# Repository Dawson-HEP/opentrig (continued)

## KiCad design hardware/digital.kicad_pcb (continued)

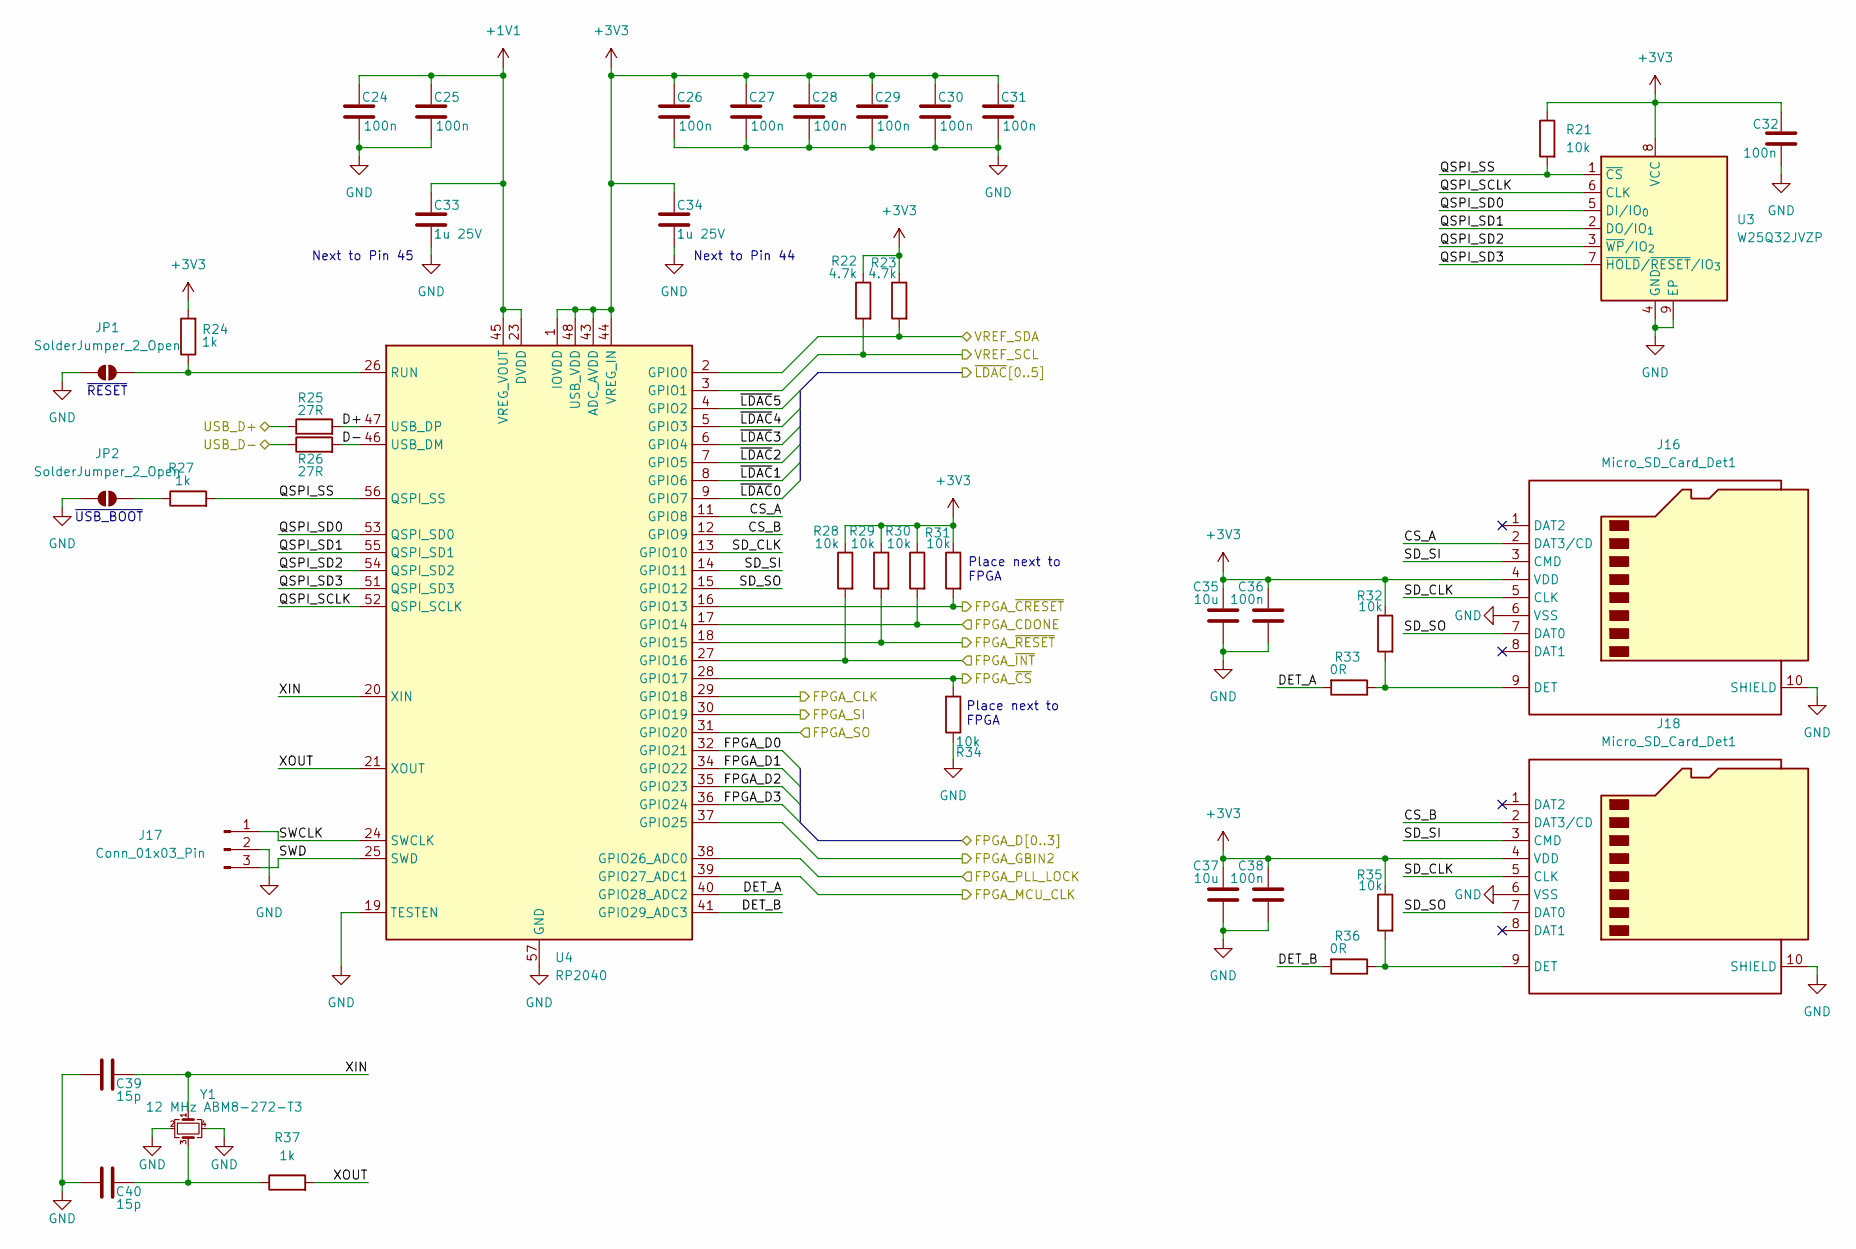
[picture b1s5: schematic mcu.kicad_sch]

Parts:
C24, C25, C26, C27, C28, C29, C30, C31, C32, C36, C38: 100n; C_0402_1005Metric; LCSC C307331
C33, C34: 1u 25V; C_0402_1005Metric; LCSC C52923
C35, C37: 10u; C_1206_3216Metric; LCSC C13585
C39, C40: 15p; C_0402_1005Metric; LCSC C1548
J16, J18: Micro_SD_Card_Det1; microSD_HC_MSD-4-A; LCSC C91145
J17: Conn_01x03_Pin; PinHeader_1x03_P2.54mm_Vertical
JP1, JP2: SolderJumper_2_Open; SolderJumper-2_P1.3mm_Open_RoundedPad1.0x1.5mm
R21, R28, R29, R30, R31, R32, R34, R35: 10k; R_0402_1005Metric; LCSC C25744
R22, R23: 4.7k; R_0402_1005Metric; LCSC C25900
R24, R27, R37: 1k; R_0402_1005Metric; LCSC C11702
R25, R26: 27R; R_0402_1005Metric; LCSC C138021
R33, R36: 0R; R_0402_1005Metric; LCSC C17168
U3: W25Q32JVZP; WSON-8-1EP_6x5mm_P1.27mm_EP3.4x4.3mm; LCSC C571260
U4: RP2040; QFN-56-1EP_7x7mm_P0.4mm_EP3.2x3.2mm; LCSC C2040
Y1: 12 MHz ABM8-272-T3; Crystal_SMD_Abracon_ABM8AIG-4Pin_3.2x2.5mm; LCSC C20625731

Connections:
+1V1: C24.1, C25.1, C33.1, U4.23 (DVDD), U4.45 (VREG_VOUT), U4.50 (DVDD)
+3V3: C26.1, C27.1, C28.1, C29.1, C30.1, C31.1, C32.1, C34.1, C35.1, C36.1, C37.1, C38.1, J16.4 (VDD), J18.4 (VDD), R21.1, R22.1, R23.1, R24.2, R28.1, R29.1, R30.1, R31.1, R32.1, R35.1, U3.8 (VCC), U4.1 (IOVDD), U4.10 (IOVDD), U4.22 (IOVDD), U4.33 (IOVDD), U4.42 (IOVDD), U4.43 (ADC_AVDD), U4.44 (VREG_IN), U4.48 (USB_VDD), U4.49 (IOVDD); also elsewhere on the board
/FPGA/CDONE: R30.2, U4.17 (GPIO14); also elsewhere on the board
/FPGA/CS: R34.2, U4.28 (GPIO17); also elsewhere on the board
/FPGA/D0: U4.32 (GPIO21); also elsewhere on the board
/FPGA/D1: U4.34 (GPIO22); also elsewhere on the board
/FPGA/D2: U4.35 (GPIO23); also elsewhere on the board
/FPGA/D3: U4.36 (GPIO24); also elsewhere on the board
/FPGA/GBIN2: U4.37 (GPIO25); also elsewhere on the board
/FPGA/MCU_CLK: U4.39 (GPIO27_ADC1); also elsewhere on the board
/FPGA/PLL_LOCK: U4.38 (GPIO26_ADC0); also elsewhere on the board
/FPGA/SCK: U4.29 (GPIO18); also elsewhere on the board
/FPGA/SI: U4.30 (GPIO19); also elsewhere on the board
/FPGA/SO: U4.31 (GPIO20); also elsewhere on the board
/FPGA/~CRESET: R31.2, U4.16 (GPIO13); also elsewhere on the board
/FPGA/~INT: R28.2, U4.27 (GPIO16); also elsewhere on the board
/FPGA/~RESET: R29.2, U4.18 (GPIO15); also elsewhere on the board
/MCU/CS_A: J16.2 (DAT3/CD), U4.11 (GPIO8)
/MCU/CS_B: J18.2 (DAT3/CD), U4.12 (GPIO9)
/MCU/D+: R25.2, U4.47 (USB_DP)
/MCU/D-: R26.2, U4.46 (USB_DM)
/MCU/DET_A: R33.2, U4.40 (GPIO28_ADC2)
/MCU/DET_B: R36.2, U4.41 (GPIO29_ADC3)
/MCU/QSPI_SCLK: U3.6 (CLK), U4.52 (QSPI_SCLK)
/MCU/QSPI_SD0: U3.5 (DI/IO_{0}), U4.53 (QSPI_SD0)
/MCU/QSPI_SD1: U3.2 (DO/IO_{1}), U4.55 (QSPI_SD1)
/MCU/QSPI_SD2: U3.3 (~WP/IO_{2}), U4.54 (QSPI_SD2)
/MCU/QSPI_SD3: U3.7 (~HOLD/~RESET/IO_{3}), U4.51 (QSPI_SD3)
/MCU/QSPI_SS: R21.2, R27.2, U3.1 (~CS), U4.56 (QSPI_SS)
/MCU/SD_CLK: J16.5 (CLK), J18.5 (CLK), U4.13 (GPIO10)
/MCU/SD_SI: J16.3 (CMD), J18.3 (CMD), U4.14 (GPIO11)
/MCU/SD_SO: J16.7 (DAT0), J18.7 (DAT0), U4.15 (GPIO12)
/MCU/SWCLK: J17.1, U4.24 (SWCLK)
/MCU/SWD: J17.3, U4.25 (SWD)
/MCU/USB_D+: R25.1; also elsewhere on the board
/MCU/USB_D-: R26.1; also elsewhere on the board
/MCU/VREF_SCL: R22.2, U4.3 (GPIO1); also elsewhere on the board
/MCU/VREF_SDA: R23.2, U4.2 (GPIO0); also elsewhere on the board
/MCU/XIN: C39.2, U4.20 (XIN), Y1.1
/MCU/XOUT: R37.2, U4.21 (XOUT)
/MCU/~LDAC0: U4.9 (GPIO7); also elsewhere on the board
/MCU/~LDAC1: U4.8 (GPIO6); also elsewhere on the board
/MCU/~LDAC2: U4.7 (GPIO5); also elsewhere on the board
/MCU/~LDAC3: U4.6 (GPIO4); also elsewhere on the board
/MCU/~LDAC4: U4.5 (GPIO3); also elsewhere on the board
/MCU/~LDAC5: U4.4 (GPIO2); also elsewhere on the board
GND: C24.2, C25.2, C26.2, C27.2, C28.2, C29.2, C30.2, C31.2, C32.2, C33.2, C34.2, C35.2, C36.2, C37.2, C38.2, C39.1, C40.1, J16.6 (VSS), J16.10 (SHIELD), J17.2, J18.6 (VSS), J18.10 (SHIELD), JP1.1 (A), JP2.1 (A), R34.1, U3.4 (GND), U3.9 (EP), U4.19 (TESTEN), U4.57 (GND), Y1.2, Y1.4; also elsewhere on the board
unnamed: C40.2, R37.1, Y1.3
unnamed: J16.9 (DET), R32.2, R33.1
unnamed: J18.9 (DET), R35.2, R36.1
unnamed: JP1.2 (B), R24.1, U4.26 (RUN)
unnamed: JP2.2 (B), R27.1

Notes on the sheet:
Place next to FPGA
Next to Pin 44
Next to Pin 45
~{USB_BOOT}
~{RESET}

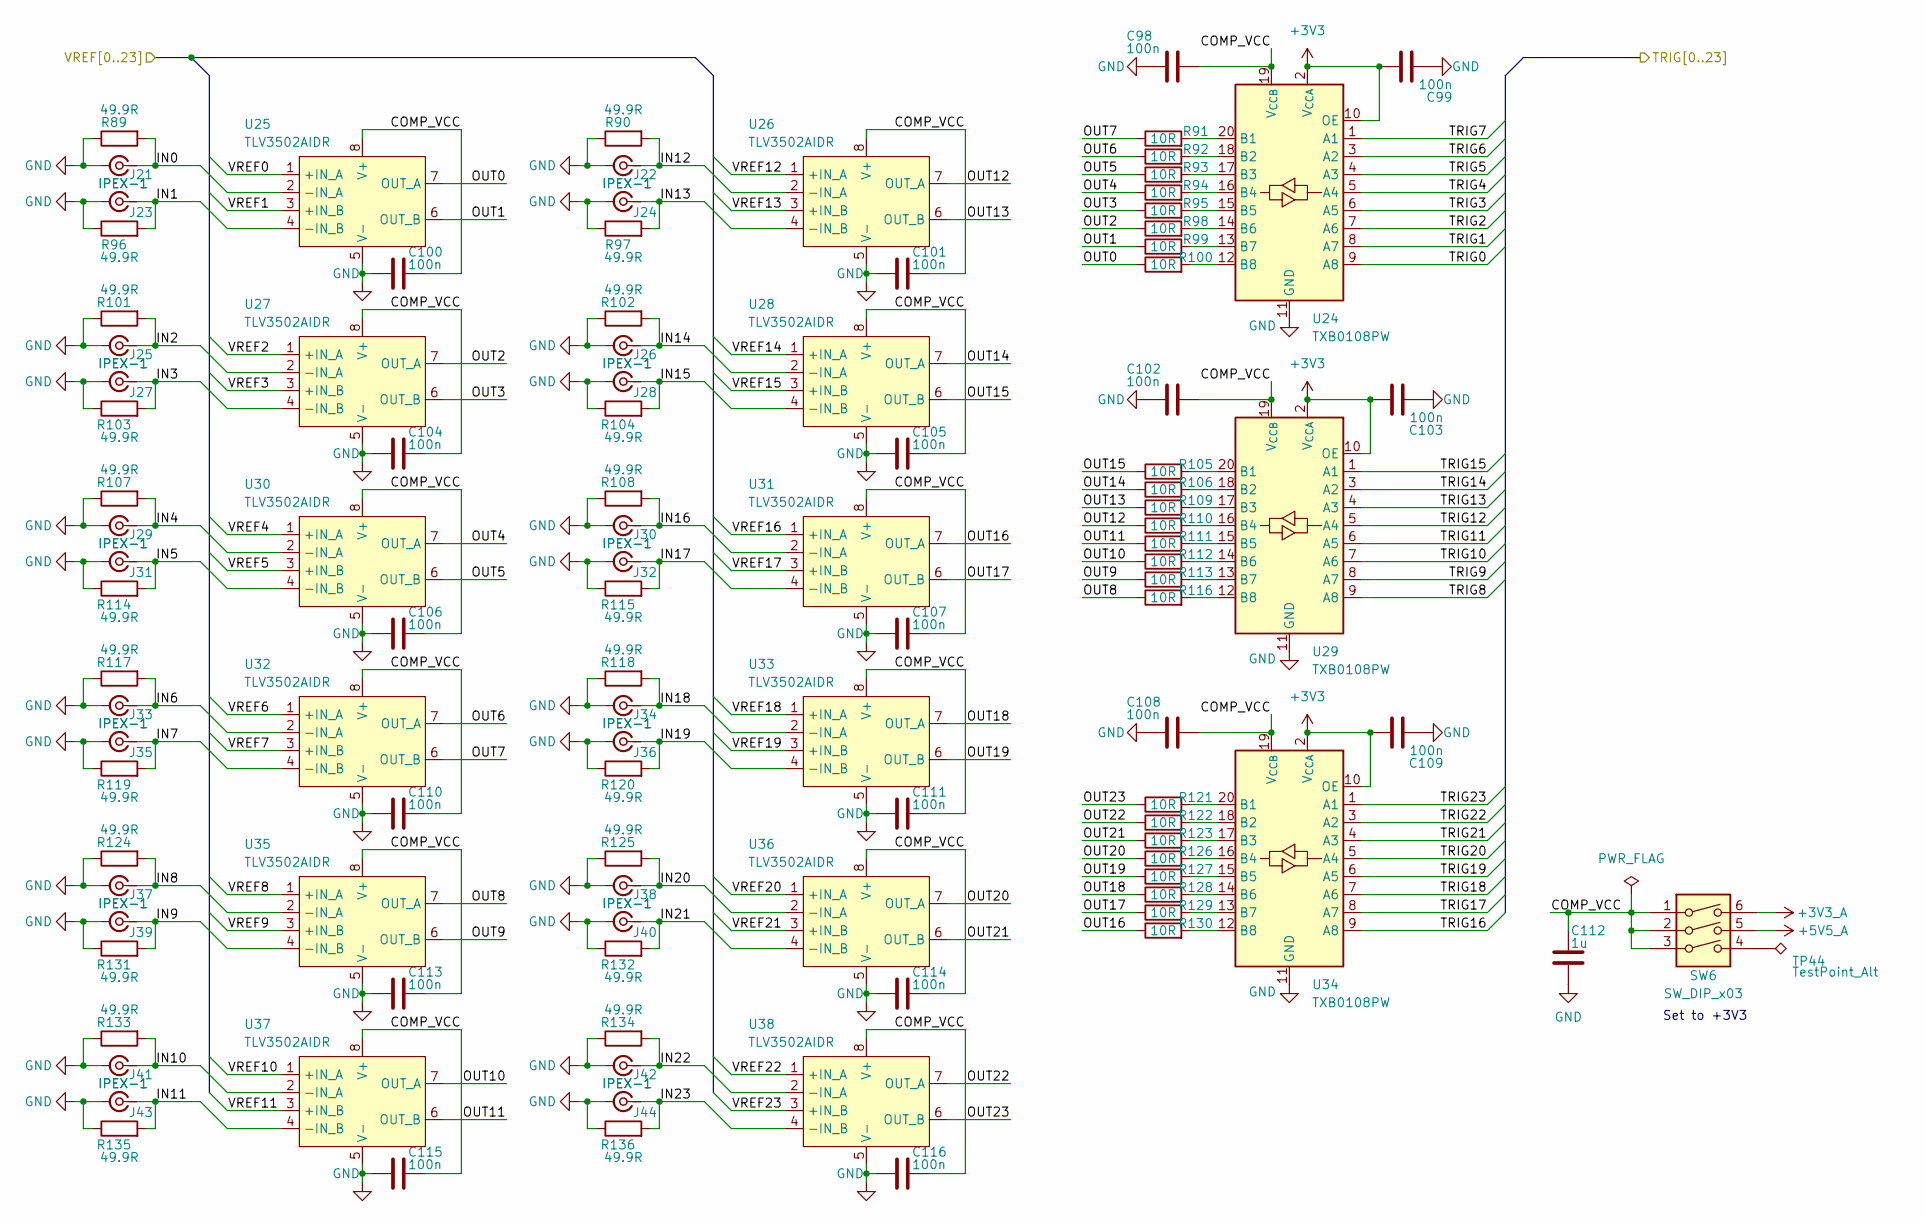
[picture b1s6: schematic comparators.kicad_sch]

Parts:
C98, C99, C100, C101, C102, C103, C104, C105, C106, C107, C108, C109, C110, C111, C113, C114, C115, C116: 100n; C_0402_1005Metric; LCSC C307331
C112: 1u; C_0805_2012Metric; LCSC C28323
J21, J22, J23, J24, J25, J26, J27, J28, J29, J30, J31, J32, J33, J34, J35, J36, J37, J38, J39, J40, J41, J42, J43, J44: IPEX-1; BWIPX-1-001E; LCSC C496552
R89, R90, R96, R97, R101, R102, R103, R104, R107, R108, R114, R115, R117, R118, R119, R120, R124, R125, R131, R132, R133, R134, R135, R136: 49.9R; R_0603_1608Metric; LCSC C23185
R91, R92, R93, R94, R95, R98, R99, R100, R105, R106, R109, R110, R111, R112, R113, R116, R121, R122, R123, R126, R127, R128, R129, R130: 10R; R_0402_1005Metric; LCSC C25077
SW6: SW_DIP_x03; SW_DIP_SPSTx03_Slide_6.7x9.18mm_W8.61mm_P2.54mm_LowProfile; LCSC C129079
TP44: TestPoint_Alt; TestPoint_Keystone_5015_Micro_Mini; LCSC C159868
U24, U29, U34: TXB0108PW; TSSOP-20_4.4x6.5mm_P0.65mm; LCSC C53406
U25, U26, U27, U28, U30, U31, U32, U33, U35, U36, U37, U38: TLV3502AIDR; SOIC-8_3.9x4.9mm_P1.27mm

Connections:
+3V3: C99.1, C103.1, C109.1, U24.2 (V_{CCA}), U24.10 (OE), U29.2 (V_{CCA}), U29.10 (OE), U34.2 (V_{CCA}), U34.10 (OE); also elsewhere on the board
+3V3_A: SW6.6; also elsewhere on the board
+5V5_A: SW6.5; also elsewhere on the board
/FPGA/TRIG_IN_0: U24.9 (A8); also elsewhere on the board
/FPGA/TRIG_IN_1: U24.8 (A7); also elsewhere on the board
/FPGA/TRIG_IN_2: U24.7 (A6); also elsewhere on the board
/FPGA/TRIG_IN_3: U24.6 (A5); also elsewhere on the board
/FPGA/TRIG_IN_4: U24.5 (A4); also elsewhere on the board
/FPGA/TRIG_IN_5: U24.4 (A3); also elsewhere on the board
/FPGA/TRIG_IN_6: U24.3 (A2); also elsewhere on the board
/FPGA/TRIG_IN_7: U24.1 (A1); also elsewhere on the board
/FPGA/TRIG_IN_8: U29.9 (A8); also elsewhere on the board
/FPGA/TRIG_IN_9: U29.8 (A7); also elsewhere on the board
/FPGA/TRIG_IN_10: U29.7 (A6); also elsewhere on the board
/FPGA/TRIG_IN_11: U29.6 (A5); also elsewhere on the board
/FPGA/TRIG_IN_12: U29.5 (A4); also elsewhere on the board
/FPGA/TRIG_IN_13: U29.4 (A3); also elsewhere on the board
/FPGA/TRIG_IN_14: U29.3 (A2); also elsewhere on the board
/FPGA/TRIG_IN_15: U29.1 (A1); also elsewhere on the board
/FPGA/TRIG_IN_16: U34.9 (A8); also elsewhere on the board
/FPGA/TRIG_IN_17: U34.8 (A7); also elsewhere on the board
/FPGA/TRIG_IN_18: U34.7 (A6); also elsewhere on the board
/FPGA/TRIG_IN_19: U34.6 (A5); also elsewhere on the board
/FPGA/TRIG_IN_20: U34.5 (A4); also elsewhere on the board
/FPGA/TRIG_IN_21: U34.4 (A3); also elsewhere on the board
/FPGA/TRIG_IN_22: U34.3 (A2); also elsewhere on the board
/FPGA/TRIG_IN_23: U34.1 (A1); also elsewhere on the board
/comparators/COMP_VCC: C98.1, C100.2, C101.2, C102.1, C104.2, C105.2, C106.2, C107.2, C108.1, C110.2, C111.2, C112.1, C113.2, C114.2, C115.2, C116.2, SW6.1, SW6.2, SW6.3, U24.19 (V_{CCB}), U25.8 (V+), U26.8 (V+), U27.8 (V+), U28.8 (V+), U29.19 (V_{CCB}), U30.8 (V+), U31.8 (V+), U32.8 (V+), U33.8 (V+), U34.19 (V_{CCB}), U35.8 (V+), U36.8 (V+), U37.8 (V+), U38.8 (V+)
/comparators/IN0: J21.1 (In), R89.2, U25.2 (-IN_A)
/comparators/IN1: J23.1 (In), R96.2, U25.4 (-IN_B)
/comparators/IN2: J25.1 (In), R101.2, U27.2 (-IN_A)
/comparators/IN3: J27.1 (In), R103.2, U27.4 (-IN_B)
/comparators/IN4: J29.1 (In), R107.2, U30.2 (-IN_A)
/comparators/IN5: J31.1 (In), R114.2, U30.4 (-IN_B)
/comparators/IN6: J33.1 (In), R117.2, U32.2 (-IN_A)
/comparators/IN7: J35.1 (In), R119.2, U32.4 (-IN_B)
/comparators/IN8: J37.1 (In), R124.2, U35.2 (-IN_A)
/comparators/IN9: J39.1 (In), R131.2, U35.4 (-IN_B)
/comparators/IN10: J41.1 (In), R133.2, U37.2 (-IN_A)
/comparators/IN11: J43.1 (In), R135.2, U37.4 (-IN_B)
/comparators/IN12: J22.1 (In), R90.2, U26.2 (-IN_A)
/comparators/IN13: J24.1 (In), R97.2, U26.4 (-IN_B)
/comparators/IN14: J26.1 (In), R102.2, U28.2 (-IN_A)
/comparators/IN15: J28.1 (In), R104.2, U28.4 (-IN_B)
/comparators/IN16: J30.1 (In), R108.2, U31.2 (-IN_A)
/comparators/IN17: J32.1 (In), R115.2, U31.4 (-IN_B)
/comparators/IN18: J34.1 (In), R118.2, U33.2 (-IN_A)
/comparators/IN19: J36.1 (In), R120.2, U33.4 (-IN_B)
/comparators/IN20: J38.1 (In), R125.2, U36.2 (-IN_A)
/comparators/IN21: J40.1 (In), R132.2, U36.4 (-IN_B)
/comparators/IN22: J42.1 (In), R134.2, U38.2 (-IN_A)
/comparators/IN23: J44.1 (In), R136.2, U38.4 (-IN_B)
/comparators/OUT0: R100.1, U25.7 (OUT_A)
/comparators/OUT1: R99.1, U25.6 (OUT_B)
/comparators/OUT2: R98.1, U27.7 (OUT_A)
/comparators/OUT3: R95.1, U27.6 (OUT_B)
/comparators/OUT4: R94.1, U30.7 (OUT_A)
/comparators/OUT5: R93.1, U30.6 (OUT_B)
/comparators/OUT6: R92.1, U32.7 (OUT_A)
/comparators/OUT7: R91.1, U32.6 (OUT_B)
/comparators/OUT8: R116.1, U35.7 (OUT_A)
/comparators/OUT9: R113.1, U35.6 (OUT_B)
/comparators/OUT10: R112.1, U37.7 (OUT_A)
/comparators/OUT11: R111.1, U37.6 (OUT_B)
/comparators/OUT12: R110.1, U26.7 (OUT_A)
/comparators/OUT13: R109.1, U26.6 (OUT_B)
/comparators/OUT14: R106.1, U28.7 (OUT_A)
/comparators/OUT15: R105.1, U28.6 (OUT_B)
/comparators/OUT16: R130.1, U31.7 (OUT_A)
/comparators/OUT17: R129.1, U31.6 (OUT_B)
/comparators/OUT18: R128.1, U33.7 (OUT_A)
/comparators/OUT19: R127.1, U33.6 (OUT_B)
/comparators/OUT20: R126.1, U36.7 (OUT_A)
/comparators/OUT21: R123.1, U36.6 (OUT_B)
/comparators/OUT22: R122.1, U38.7 (OUT_A)
/comparators/OUT23: R121.1, U38.6 (OUT_B)
/comparators/VREF0: U25.1 (+IN_A); also elsewhere on the board
/comparators/VREF1: U25.3 (+IN_B); also elsewhere on the board
/comparators/VREF2: U27.1 (+IN_A); also elsewhere on the board
/comparators/VREF3: U27.3 (+IN_B); also elsewhere on the board
/comparators/VREF4: U30.1 (+IN_A); also elsewhere on the board
/comparators/VREF5: U30.3 (+IN_B); also elsewhere on the board
/comparators/VREF6: U32.1 (+IN_A); also elsewhere on the board
/comparators/VREF7: U32.3 (+IN_B); also elsewhere on the board
/comparators/VREF8: U35.1 (+IN_A); also elsewhere on the board
/comparators/VREF9: U35.3 (+IN_B); also elsewhere on the board
/comparators/VREF10: U37.1 (+IN_A); also elsewhere on the board
/comparators/VREF11: U37.3 (+IN_B); also elsewhere on the board
/comparators/VREF12: U26.1 (+IN_A); also elsewhere on the board
/comparators/VREF13: U26.3 (+IN_B); also elsewhere on the board
/comparators/VREF14: U28.1 (+IN_A); also elsewhere on the board
/comparators/VREF15: U28.3 (+IN_B); also elsewhere on the board
/comparators/VREF16: U31.1 (+IN_A); also elsewhere on the board
/comparators/VREF17: U31.3 (+IN_B); also elsewhere on the board
/comparators/VREF18: U33.1 (+IN_A); also elsewhere on the board
/comparators/VREF19: U33.3 (+IN_B); also elsewhere on the board
/comparators/VREF20: U36.1 (+IN_A); also elsewhere on the board
/comparators/VREF21: U36.3 (+IN_B); also elsewhere on the board
/comparators/VREF22: U38.1 (+IN_A); also elsewhere on the board
/comparators/VREF23: U38.3 (+IN_B); also elsewhere on the board
GND: C98.2, C99.2, C100.1, C101.1, C102.2, C103.2, C104.1, C105.1, C106.1, C107.1, C108.2, C109.2, C110.1, C111.1, C112.2, C113.1, C114.1, C115.1, C116.1, J21.2 (Ext), J22.2 (Ext), J23.2 (Ext), J24.2 (Ext), J25.2 (Ext), J26.2 (Ext), J27.2 (Ext), J28.2 (Ext), J29.2 (Ext), J30.2 (Ext), J31.2 (Ext), J32.2 (Ext), J33.2 (Ext), J34.2 (Ext), J35.2 (Ext), J36.2 (Ext), J37.2 (Ext), J38.2 (Ext), J39.2 (Ext), J40.2 (Ext), J41.2 (Ext), J42.2 (Ext), J43.2 (Ext), J44.2 (Ext), R89.1, R90.1, R96.1, R97.1, R101.1, R102.1, R103.1, R104.1, R107.1, R108.1, R114.1, R115.1, R117.1, R118.1, R119.1, R120.1, R124.1, R125.1, R131.1, R132.1, R133.1, R134.1, R135.1, R136.1, U24.11 (GND), U25.5 (V-), U26.5 (V-), U27.5 (V-), U28.5 (V-), U29.11 (GND), U30.5 (V-), U31.5 (V-), U32.5 (V-), U33.5 (V-), U34.11 (GND), U35.5 (V-), U36.5 (V-), U37.5 (V-), U38.5 (V-); also elsewhere on the board
unnamed: SW6.4, TP44.1
unnamed: R91.2, U24.20 (B1)
unnamed: R92.2, U24.18 (B2)
unnamed: R93.2, U24.17 (B3)
unnamed: R94.2, U24.16 (B4)
unnamed: R95.2, U24.15 (B5)
unnamed: R98.2, U24.14 (B6)
unnamed: R99.2, U24.13 (B7)
unnamed: R100.2, U24.12 (B8)
unnamed: R105.2, U29.20 (B1)
unnamed: R106.2, U29.18 (B2)
unnamed: R109.2, U29.17 (B3)
unnamed: R110.2, U29.16 (B4)
unnamed: R111.2, U29.15 (B5)
unnamed: R112.2, U29.14 (B6)
unnamed: R113.2, U29.13 (B7)
unnamed: R116.2, U29.12 (B8)
unnamed: R121.2, U34.20 (B1)
unnamed: R122.2, U34.18 (B2)
unnamed: R123.2, U34.17 (B3)
unnamed: R126.2, U34.16 (B4)
unnamed: R127.2, U34.15 (B5)
unnamed: R128.2, U34.14 (B6)
unnamed: R129.2, U34.13 (B7)
unnamed: R130.2, U34.12 (B8)

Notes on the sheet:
Set to +3V3

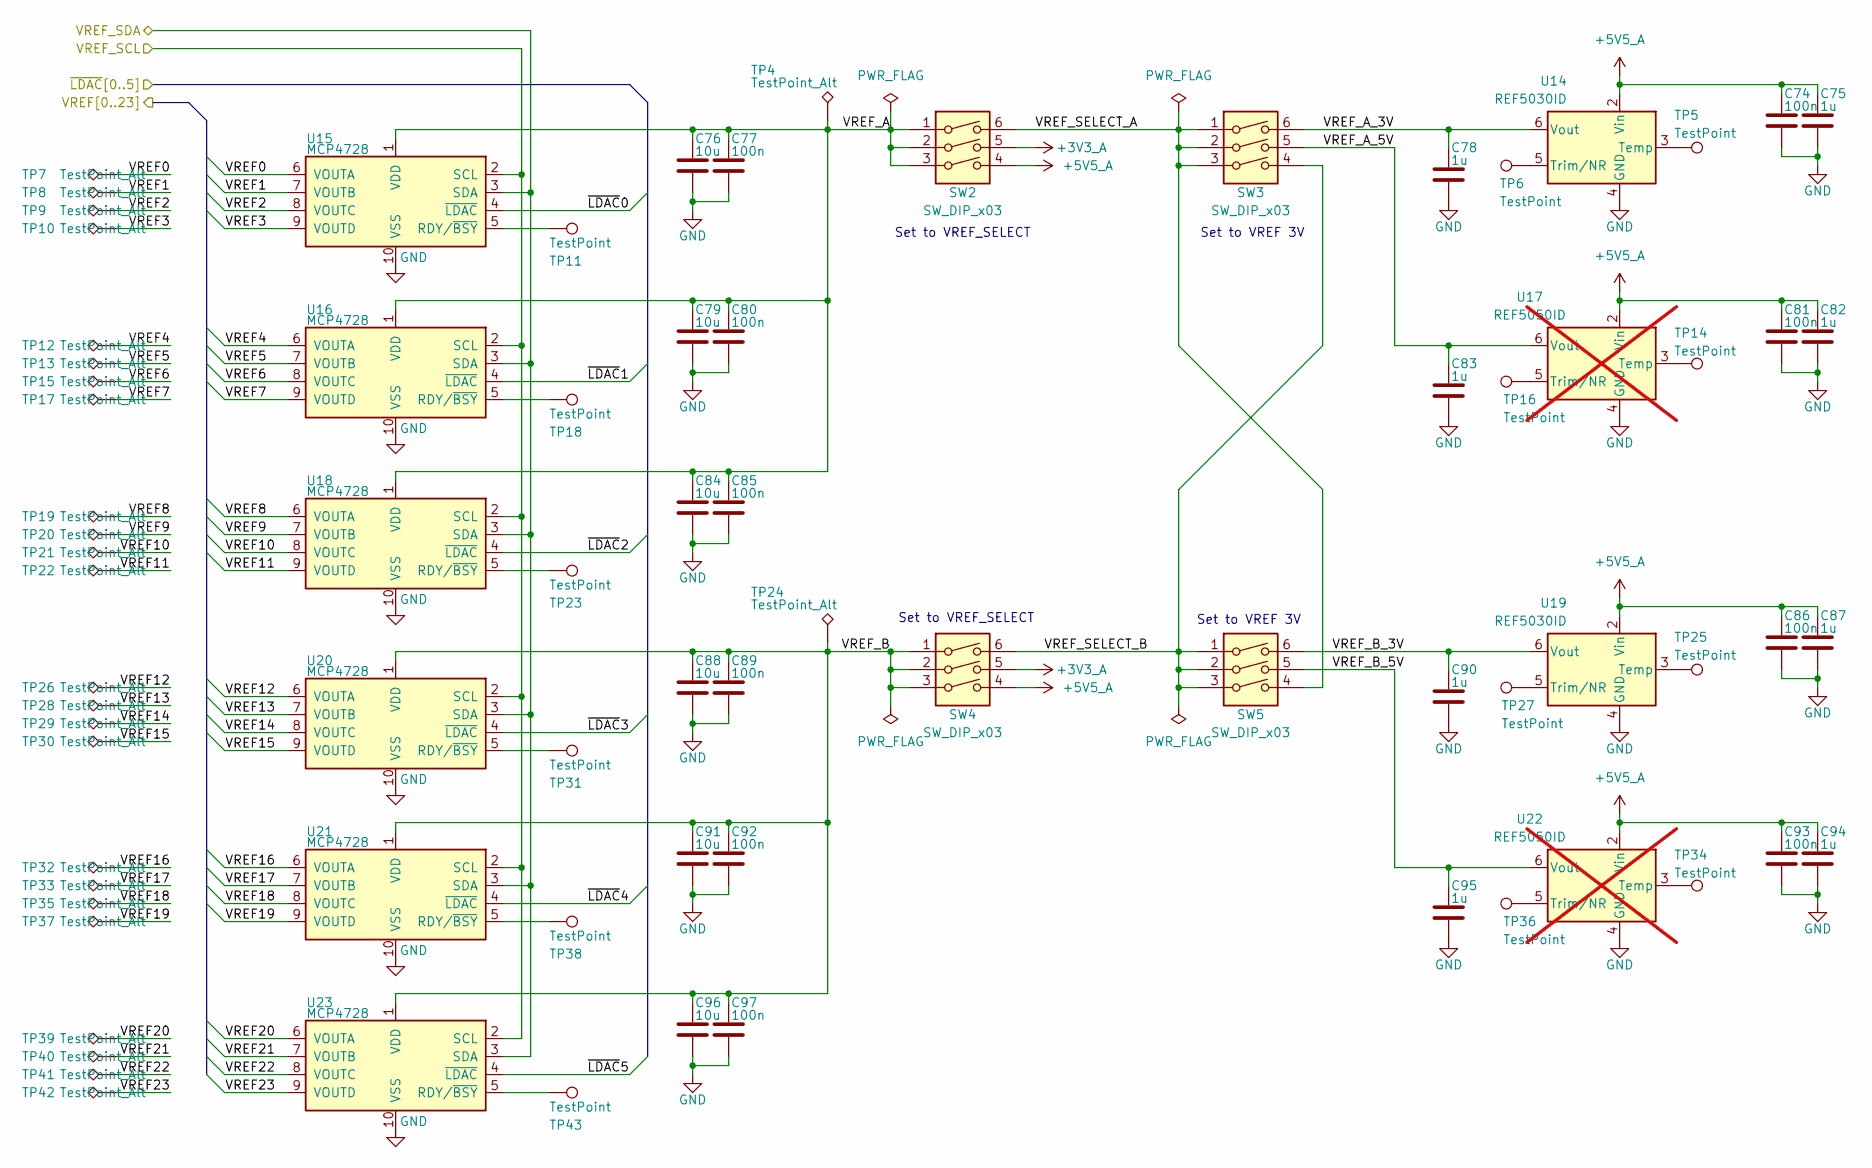
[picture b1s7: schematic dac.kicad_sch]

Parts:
C74, C77, C80, C81, C85, C86, C89, C92, C93, C97: 100n; C_0402_1005Metric; LCSC C307331
C75, C78, C82, C83, C87, C90, C94, C95: 1u; C_0805_2012Metric; LCSC C28323
C76, C79, C84, C88, C91, C96: 10u; C_1206_3216Metric; LCSC C13585
SW2, SW3, SW4, SW5: SW_DIP_x03; SW_DIP_SPSTx03_Slide_6.7x9.18mm_W8.61mm_P2.54mm_LowProfile; LCSC C129079
TP4, TP7, TP8, TP9, TP10, TP12, TP13, TP15, TP17, TP19, TP20, TP21, TP22, TP24, TP26, TP28, TP29, TP30, TP32, TP33, TP35, TP37, TP39, TP40, TP41, TP42: TestPoint_Alt; TestPoint_Keystone_5015_Micro_Mini; LCSC C159868
TP5, TP6, TP11, TP14, TP16, TP18, TP23, TP25, TP27, TP31, TP34, TP36, TP38, TP43: TestPoint; TestPoint_Pad_D1.0mm
U14, U19: REF5030ID; SOIC-8_3.9x4.9mm_P1.27mm; LCSC C2878155
U15, U16, U18, U20, U21, U23: MCP4728; MSOP-10_3x3mm_P0.5mm; LCSC C108207
U17, U22: REF5050ID; SOIC-8_3.9x4.9mm_P1.27mm; not fitted

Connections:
+3V3_A: SW2.5, SW4.5; also elsewhere on the board
+5V5_A: C74.1, C75.1, C81.1, C82.1, C86.1, C87.1, C93.1, C94.1, SW2.4, SW4.4, U14.2 (Vin), U17.2 (Vin), U19.2 (Vin), U22.2 (Vin); also elsewhere on the board
/MCU/VREF_SCL: U15.2 (SCL), U16.2 (SCL), U18.2 (SCL), U20.2 (SCL), U21.2 (SCL), U23.2 (SCL); also elsewhere on the board
/MCU/VREF_SDA: U15.3 (SDA), U16.3 (SDA), U18.3 (SDA), U20.3 (SDA), U21.3 (SDA), U23.3 (SDA); also elsewhere on the board
/MCU/~LDAC0: U15.4 (~LDAC); also elsewhere on the board
/MCU/~LDAC1: U16.4 (~LDAC); also elsewhere on the board
/MCU/~LDAC2: U18.4 (~LDAC); also elsewhere on the board
/MCU/~LDAC3: U20.4 (~LDAC); also elsewhere on the board
/MCU/~LDAC4: U21.4 (~LDAC); also elsewhere on the board
/MCU/~LDAC5: U23.4 (~LDAC); also elsewhere on the board
/comparators/VREF0: TP7.1, U15.6 (VOUTA); also elsewhere on the board
/comparators/VREF1: TP8.1, U15.7 (VOUTB); also elsewhere on the board
/comparators/VREF2: TP9.1, U15.8 (VOUTC); also elsewhere on the board
/comparators/VREF3: TP10.1, U15.9 (VOUTD); also elsewhere on the board
/comparators/VREF4: TP12.1, U16.6 (VOUTA); also elsewhere on the board
/comparators/VREF5: TP13.1, U16.7 (VOUTB); also elsewhere on the board
/comparators/VREF6: TP15.1, U16.8 (VOUTC); also elsewhere on the board
/comparators/VREF7: TP17.1, U16.9 (VOUTD); also elsewhere on the board
/comparators/VREF8: TP19.1, U18.6 (VOUTA); also elsewhere on the board
/comparators/VREF9: TP20.1, U18.7 (VOUTB); also elsewhere on the board
/comparators/VREF10: TP21.1, U18.8 (VOUTC); also elsewhere on the board
/comparators/VREF11: TP22.1, U18.9 (VOUTD); also elsewhere on the board
/comparators/VREF12: TP26.1, U20.6 (VOUTA); also elsewhere on the board
/comparators/VREF13: TP28.1, U20.7 (VOUTB); also elsewhere on the board
/comparators/VREF14: TP29.1, U20.8 (VOUTC); also elsewhere on the board
/comparators/VREF15: TP30.1, U20.9 (VOUTD); also elsewhere on the board
/comparators/VREF16: TP32.1, U21.6 (VOUTA); also elsewhere on the board
/comparators/VREF17: TP33.1, U21.7 (VOUTB); also elsewhere on the board
/comparators/VREF18: TP35.1, U21.8 (VOUTC); also elsewhere on the board
/comparators/VREF19: TP37.1, U21.9 (VOUTD); also elsewhere on the board
/comparators/VREF20: TP39.1, U23.6 (VOUTA); also elsewhere on the board
/comparators/VREF21: TP40.1, U23.7 (VOUTB); also elsewhere on the board
/comparators/VREF22: TP41.1, U23.8 (VOUTC); also elsewhere on the board
/comparators/VREF23: TP42.1, U23.9 (VOUTD); also elsewhere on the board
/dac/VREF_A: C76.1, C77.1, C79.1, C80.1, C84.1, C85.1, SW2.1, SW2.2, SW2.3, TP4.1, U15.1 (VDD), U16.1 (VDD), U18.1 (VDD)
/dac/VREF_A_3V: C78.1, SW3.6, U14.6 (Vout)
/dac/VREF_A_5V: C83.1, SW3.5, U17.6 (Vout)
/dac/VREF_B: C88.1, C89.1, C91.1, C92.1, C96.1, C97.1, SW4.1, SW4.2, SW4.3, TP24.1, U20.1 (VDD), U21.1 (VDD), U23.1 (VDD)
/dac/VREF_B_3V: C90.1, SW5.6, U19.6 (Vout)
/dac/VREF_B_5V: C95.1, SW5.5, U22.6 (Vout)
/dac/VREF_SELECT_A: SW2.6, SW3.1, SW3.2, SW3.3, SW5.4
/dac/VREF_SELECT_B: SW3.4, SW4.6, SW5.1, SW5.2, SW5.3
GND: C74.2, C75.2, C76.2, C77.2, C78.2, C79.2, C80.2, C81.2, C82.2, C83.2, C84.2, C85.2, C86.2, C87.2, C88.2, C89.2, C90.2, C91.2, C92.2, C93.2, C94.2, C95.2, C96.2, C97.2, U14.4 (GND), U15.10 (VSS), U16.10 (VSS), U17.4 (GND), U18.10 (VSS), U19.4 (GND), U20.10 (VSS), U21.10 (VSS), U22.4 (GND), U23.10 (VSS); also elsewhere on the board
unnamed: TP5.1, U14.3 (Temp)
unnamed: TP6.1, U14.5 (Trim/NR)
unnamed: TP11.1, U15.5 (RDY/~BSY)
unnamed: TP18.1, U16.5 (RDY/~BSY)
unnamed: TP14.1, U17.3 (Temp)
unnamed: TP16.1, U17.5 (Trim/NR)
unnamed: TP23.1, U18.5 (RDY/~BSY)
unnamed: TP25.1, U19.3 (Temp)
unnamed: TP27.1, U19.5 (Trim/NR)
unnamed: TP31.1, U20.5 (RDY/~BSY)
unnamed: TP38.1, U21.5 (RDY/~BSY)
unnamed: TP34.1, U22.3 (Temp)
unnamed: TP36.1, U22.5 (Trim/NR)
unnamed: TP43.1, U23.5 (RDY/~BSY)

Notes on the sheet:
Set to VREF_SELECT
Set to VREF 3V

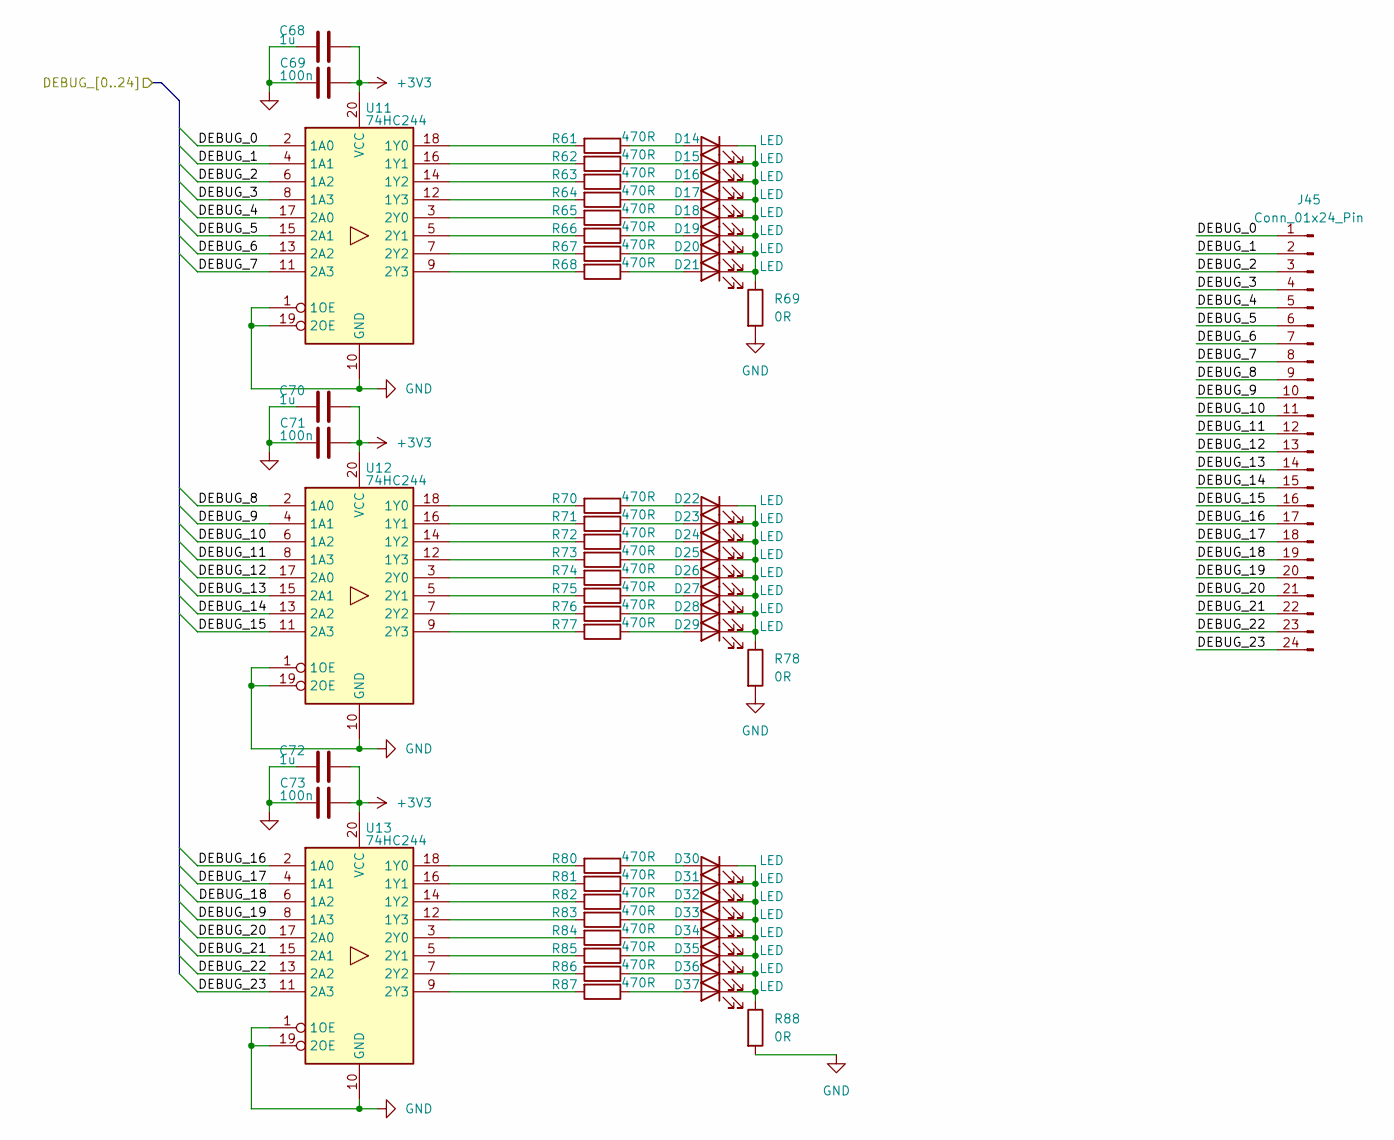
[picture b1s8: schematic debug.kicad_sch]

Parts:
C68, C70, C72: 1u; C_0805_2012Metric; LCSC C28323
C69, C71, C73: 100n; C_0402_1005Metric; LCSC C307331
D14, D15, D16, D17, D18, D19, D20, D21, D22, D23, D24, D25, D26, D27, D28, D29, D30, D31, D32, D33, D34, D35, D36, D37: LED; LED_0805_2012Metric; LCSC C2297
J45: Conn_01x24_Pin; PinHeader_1x24_P2.54mm_Vertical
R61, R62, R63, R64, R65, R66, R67, R68, R70, R71, R72, R73, R74, R75, R76, R77, R80, R81, R82, R83, R84, R85, R86, R87: 470R; R_0402_1005Metric; LCSC C25117
R69, R78, R88: 0R; R_0402_1005Metric; LCSC C17168
U11, U12, U13: 74HC244; TSSOP-20_4.4x6.5mm_P0.65mm; LCSC C6835

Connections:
+3V3: C68.2, C69.2, C70.2, C71.2, C72.2, C73.2, U11.20 (VCC), U12.20 (VCC), U13.20 (VCC); also elsewhere on the board
/FPGA/DEBUG_0: J45.1, U11.2 (1A0); also elsewhere on the board
/FPGA/DEBUG_1: J45.2, U11.4 (1A1); also elsewhere on the board
/FPGA/DEBUG_2: J45.3, U11.6 (1A2); also elsewhere on the board
/FPGA/DEBUG_3: J45.4, U11.8 (1A3); also elsewhere on the board
/FPGA/DEBUG_4: J45.5, U11.17 (2A0); also elsewhere on the board
/FPGA/DEBUG_5: J45.6, U11.15 (2A1); also elsewhere on the board
/FPGA/DEBUG_6: J45.7, U11.13 (2A2); also elsewhere on the board
/FPGA/DEBUG_7: J45.8, U11.11 (2A3); also elsewhere on the board
/FPGA/DEBUG_8: J45.9, U12.2 (1A0); also elsewhere on the board
/FPGA/DEBUG_9: J45.10, U12.4 (1A1); also elsewhere on the board
/FPGA/DEBUG_10: J45.11, U12.6 (1A2); also elsewhere on the board
/FPGA/DEBUG_11: J45.12, U12.8 (1A3); also elsewhere on the board
/FPGA/DEBUG_12: J45.13, U12.17 (2A0); also elsewhere on the board
/FPGA/DEBUG_13: J45.14, U12.15 (2A1); also elsewhere on the board
/FPGA/DEBUG_14: J45.15, U12.13 (2A2); also elsewhere on the board
/FPGA/DEBUG_15: J45.16, U12.11 (2A3); also elsewhere on the board
/FPGA/DEBUG_16: J45.17, U13.2 (1A0); also elsewhere on the board
/FPGA/DEBUG_17: J45.18, U13.4 (1A1); also elsewhere on the board
/FPGA/DEBUG_18: J45.19, U13.6 (1A2); also elsewhere on the board
/FPGA/DEBUG_19: J45.20, U13.8 (1A3); also elsewhere on the board
/FPGA/DEBUG_20: J45.21, U13.17 (2A0); also elsewhere on the board
/FPGA/DEBUG_21: J45.22, U13.15 (2A1); also elsewhere on the board
/FPGA/DEBUG_22: J45.23, U13.13 (2A2); also elsewhere on the board
/FPGA/DEBUG_23: J45.24, U13.11 (2A3); also elsewhere on the board
GND: C68.1, C69.1, C70.1, C71.1, C72.1, C73.1, R69.2, R78.2, R88.2, U11.1 (1OE), U11.10 (GND), U11.19 (2OE), U12.1 (1OE), U12.10 (GND), U12.19 (2OE), U13.1 (1OE), U13.10 (GND), U13.19 (2OE); also elsewhere on the board
unnamed: D14.2 (A), R61.1
unnamed: D14.1 (K), D15.1 (K), D16.1 (K), D17.1 (K), D18.1 (K), D19.1 (K), D20.1 (K), D21.1 (K), R69.1
unnamed: D15.2 (A), R62.1
unnamed: D16.2 (A), R63.1
unnamed: D17.2 (A), R64.1
unnamed: D18.2 (A), R65.1
unnamed: D19.2 (A), R66.1
unnamed: D20.2 (A), R67.1
unnamed: D21.2 (A), R68.1
unnamed: D22.2 (A), R70.1
unnamed: D22.1 (K), D23.1 (K), D24.1 (K), D25.1 (K), D26.1 (K), D27.1 (K), D28.1 (K), D29.1 (K), R78.1
unnamed: D23.2 (A), R71.1
unnamed: D24.2 (A), R72.1
unnamed: D25.2 (A), R73.1
unnamed: D26.2 (A), R74.1
unnamed: D27.2 (A), R75.1
unnamed: D28.2 (A), R76.1
unnamed: D29.2 (A), R77.1
unnamed: D30.2 (A), R80.1
unnamed: D30.1 (K), D31.1 (K), D32.1 (K), D33.1 (K), D34.1 (K), D35.1 (K), D36.1 (K), D37.1 (K), R88.1
unnamed: D31.2 (A), R81.1
unnamed: D32.2 (A), R82.1
unnamed: D33.2 (A), R83.1
unnamed: D34.2 (A), R84.1
unnamed: D35.2 (A), R85.1
unnamed: D36.2 (A), R86.1
unnamed: D37.2 (A), R87.1
unnamed: R61.2, U11.18 (1Y0)
unnamed: R62.2, U11.16 (1Y1)
unnamed: R63.2, U11.14 (1Y2)
unnamed: R64.2, U11.12 (1Y3)
unnamed: R65.2, U11.3 (2Y0)
unnamed: R66.2, U11.5 (2Y1)
unnamed: R67.2, U11.7 (2Y2)
unnamed: R68.2, U11.9 (2Y3)
unnamed: R70.2, U12.18 (1Y0)
unnamed: R71.2, U12.16 (1Y1)
unnamed: R72.2, U12.14 (1Y2)
unnamed: R73.2, U12.12 (1Y3)
unnamed: R74.2, U12.3 (2Y0)
unnamed: R75.2, U12.5 (2Y1)
unnamed: R76.2, U12.7 (2Y2)
unnamed: R77.2, U12.9 (2Y3)
unnamed: R80.2, U13.18 (1Y0)
unnamed: R81.2, U13.16 (1Y1)
unnamed: R82.2, U13.14 (1Y2)
unnamed: R83.2, U13.12 (1Y3)
unnamed: R84.2, U13.3 (2Y0)
unnamed: R85.2, U13.5 (2Y1)
unnamed: R86.2, U13.7 (2Y2)
unnamed: R87.2, U13.9 (2Y3)
